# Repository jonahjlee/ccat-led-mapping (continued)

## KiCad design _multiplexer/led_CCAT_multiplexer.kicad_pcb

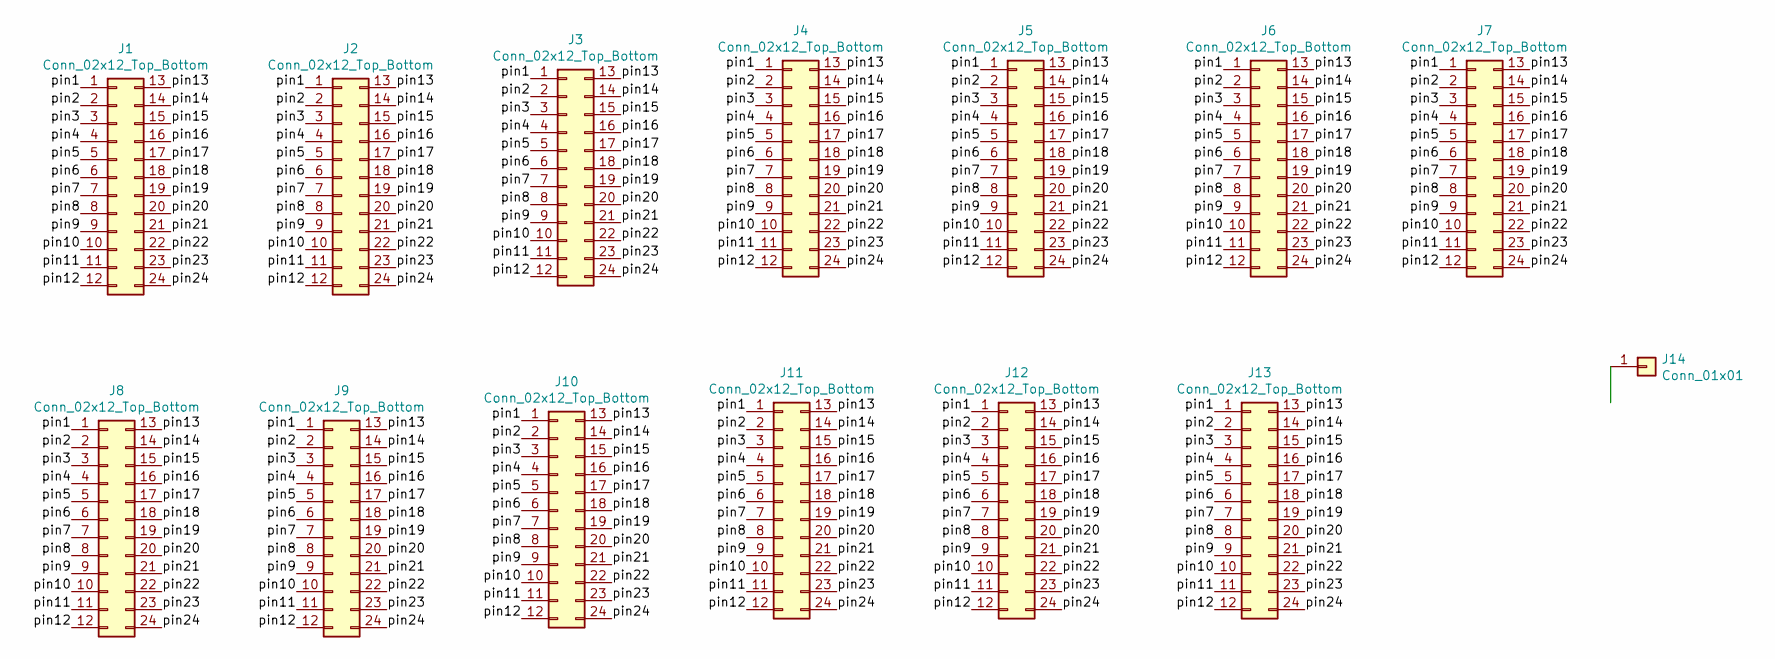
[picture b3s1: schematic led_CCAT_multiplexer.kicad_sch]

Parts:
J1, J2, J3, J4, J5, J6, J7, J8, J9, J10, J11, J12, J13: Conn_02x12_Top_Bottom; PinSocket_2x12_P2.54mm_Vertical
J14: Conn_01x01; TestPoint_Pad_1.0x1.0mm

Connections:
/pin1: J1.1, J2.1, J3.1, J4.1, J5.1, J6.1, J7.1, J8.1, J9.1, J10.1, J11.1, J12.1, J13.1, J14.1
/pin2: J1.2, J2.2, J3.2, J4.2, J5.2, J6.2, J7.2, J8.2, J9.2, J10.2, J11.2, J12.2, J13.2, J14.2
/pin3: J1.3, J2.3, J3.3, J4.3, J5.3, J6.3, J7.3, J8.3, J9.3, J10.3, J11.3, J12.3, J13.3, J14.3
/pin4: J1.4, J2.4, J3.4, J4.4, J5.4, J6.4, J7.4, J8.4, J9.4, J10.4, J11.4, J12.4, J13.4, J14.4
/pin5: J1.5, J2.5, J3.5, J4.5, J5.5, J6.5, J7.5, J8.5, J9.5, J10.5, J11.5, J12.5, J13.5, J14.5
/pin6: J1.6, J2.6, J3.6, J4.6, J5.6, J6.6, J7.6, J8.6, J9.6, J10.6, J11.6, J12.6, J13.6, J14.6
/pin7: J1.7, J2.7, J3.7, J4.7, J5.7, J6.7, J7.7, J8.7, J9.7, J10.7, J11.7, J12.7, J13.7, J14.7
/pin8: J1.8, J2.8, J3.8, J4.8, J5.8, J6.8, J7.8, J8.8, J9.8, J10.8, J11.8, J12.8, J13.8, J14.8
/pin9: J1.9, J2.9, J3.9, J4.9, J5.9, J6.9, J7.9, J8.9, J9.9, J10.9, J11.9, J12.9, J13.9, J14.9
/pin10: J1.10, J2.10, J3.10, J4.10, J5.10, J6.10, J7.10, J8.10, J9.10, J10.10, J11.10, J12.10, J13.10, J14.10
/pin11: J1.11, J2.11, J3.11, J4.11, J5.11, J6.11, J7.11, J8.11, J9.11, J10.11, J11.11, J12.11, J13.11, J14.11
/pin12: J1.12, J2.12, J3.12, J4.12, J5.12, J6.12, J7.12, J8.12, J9.12, J10.12, J11.12, J12.12, J13.12, J14.12
/pin13: J1.13, J2.13, J3.13, J4.13, J5.13, J6.13, J7.13, J8.13, J9.13, J10.13, J11.13, J12.13, J13.13, J14.14
/pin14: J1.14, J2.14, J3.14, J4.14, J5.14, J6.14, J7.14, J8.14, J9.14, J10.14, J11.14, J12.14, J13.14, J14.15
/pin15: J1.15, J2.15, J3.15, J4.15, J5.15, J6.15, J7.15, J8.15, J9.15, J10.15, J11.15, J12.15, J13.15, J14.16
/pin16: J1.16, J2.16, J3.16, J4.16, J5.16, J6.16, J7.16, J8.16, J9.16, J10.16, J11.16, J12.16, J13.16, J14.17
/pin17: J1.17, J2.17, J3.17, J4.17, J5.17, J6.17, J7.17, J8.17, J9.17, J10.17, J11.17, J12.17, J13.17, J14.18
/pin18: J1.18, J2.18, J3.18, J4.18, J5.18, J6.18, J7.18, J8.18, J9.18, J10.18, J11.18, J12.18, J13.18, J14.19
/pin19: J1.19, J2.19, J3.19, J4.19, J5.19, J6.19, J7.19, J8.19, J9.19, J10.19, J11.19, J12.19, J13.19, J14.20
/pin20: J1.20, J2.20, J3.20, J4.20, J5.20, J6.20, J7.20, J8.20, J9.20, J10.20, J11.20, J12.20, J13.20, J14.21
/pin21: J1.21, J2.21, J3.21, J4.21, J5.21, J6.21, J7.21, J8.21, J9.21, J10.21, J11.21, J12.21, J13.21, J14.22
/pin22: J1.22, J2.22, J3.22, J4.22, J5.22, J6.22, J7.22, J8.22, J9.22, J10.22, J11.22, J12.22, J13.22, J14.23
/pin23: J1.23, J2.23, J3.23, J4.23, J5.23, J6.23, J7.23, J8.23, J9.23, J10.23, J11.23, J12.23, J13.23, J14.24
/pin24: J1.24, J2.24, J3.24, J4.24, J5.24, J6.24, J7.24, J8.24, J9.24, J10.24, J11.24, J12.24, J13.24, J14.25
GND: J14.0 (PAD), J14.13

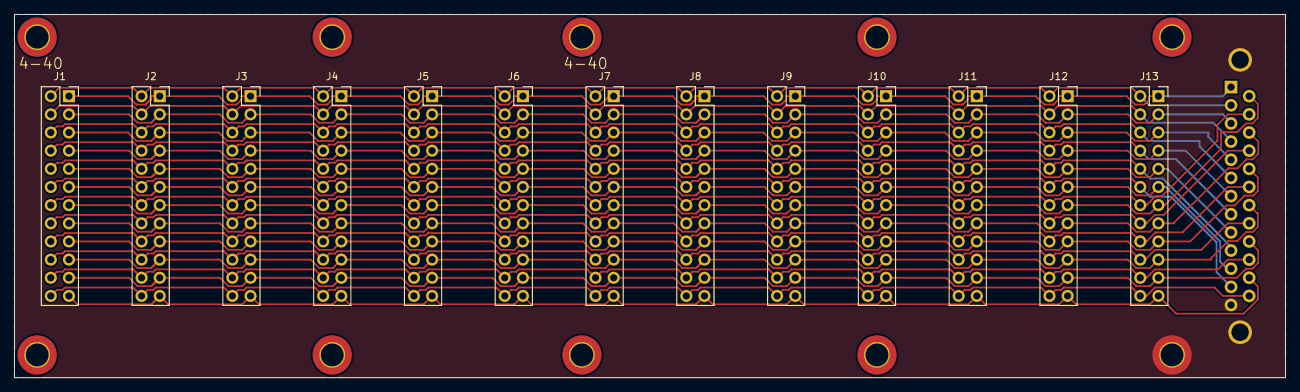
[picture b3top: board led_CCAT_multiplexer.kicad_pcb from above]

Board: 2 copper layers, 177.8 x 50.8 mm, 14 parts (1 on the bottom side), 25 nets.
